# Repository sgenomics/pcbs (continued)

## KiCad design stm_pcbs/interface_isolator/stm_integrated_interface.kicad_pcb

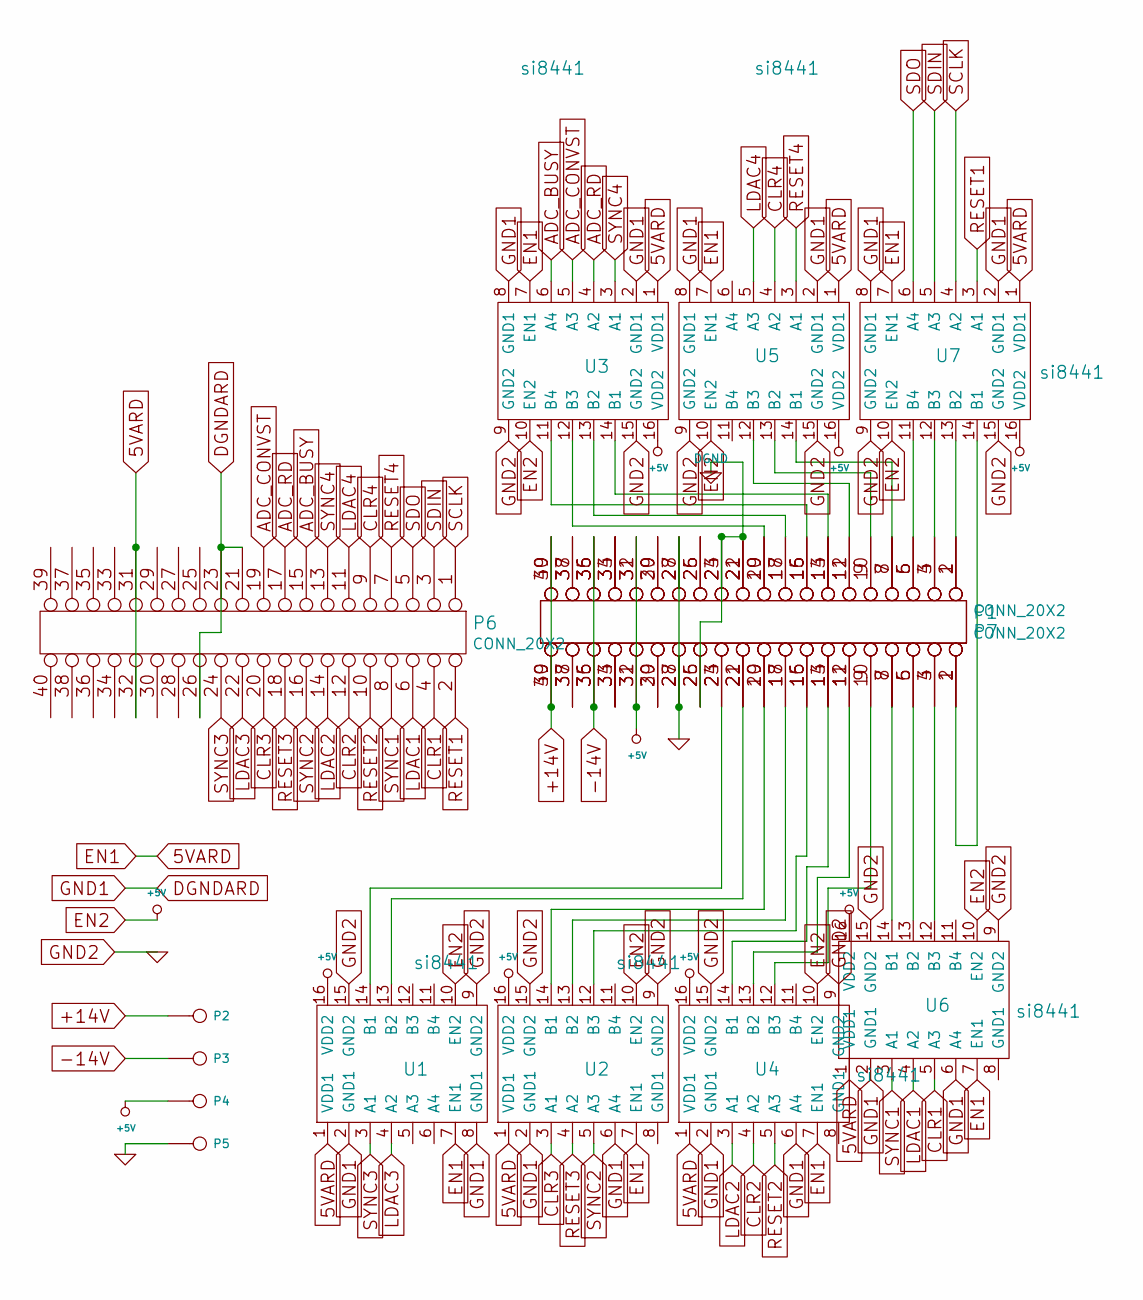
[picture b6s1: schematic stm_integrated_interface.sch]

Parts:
P1, P6, P7: CONN_20X2; IDC-Header_2x20_Pitch2.54mm_Straight
P2, P3, P4, P5: CONN_1; 4mm_banana
U1, U2, U3, U4, U5, U6, U7: si8441; SOIC-16W_7.5x10.3mm_Pitch1.27mm

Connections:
5VARD: P6.31, P6.32, U1.1 (VDD1), U1.7 (EN1), U2.1 (VDD1), U2.7 (EN1), U3.1 (VDD1), U3.7 (EN1), U4.1 (VDD1), U4.7 (EN1), U5.1 (VDD1), U5.7 (EN1), U6.1 (VDD1), U6.7 (EN1), U7.1 (VDD1), U7.7 (EN1)
+14V: P1.39, P1.40, P2.1, P7.39, P7.40
-14V: P1.35, P1.36, P3.1, P7.35, P7.36
ADC_BUSY: P6.15, U3.6 (A4)
ADC_CONVST: P6.19, U3.5 (A3)
ADC_RD: P6.17, U3.4 (A2)
CLR1: P6.4, U6.5 (A3)
CLR2: P6.12, U4.4 (A2)
CLR3: P6.20, U2.3 (A1)
CLR4: P6.9, U5.4 (A2)
DGND: P1.21, P1.23, P1.26, P7.22, P7.24, P7.25
DGNDARD: P6.21, P6.23, P6.26, U1.2 (GND1), U1.8 (GND1), U2.2 (GND1), U2.6 (A4), U3.2 (GND1), U3.8 (GND1), U4.2 (GND1), U4.6 (A4), U5.2 (GND1), U5.8 (GND1), U6.2 (GND1), U6.6 (A4), U7.2 (GND1), U7.8 (GND1)
EN2: P1.31, P1.32, P4.1, P7.31, P7.32, U1.10 (EN2), U1.16 (VDD2), U2.10 (EN2), U2.16 (VDD2), U3.10 (EN2), U3.16 (VDD2), U4.10 (EN2), U4.16 (VDD2), U5.10 (EN2), U5.16 (VDD2), U6.10 (EN2), U6.16 (VDD2), U7.10 (EN2), U7.16 (VDD2)
GND2: P1.27, P1.28, P5.1, P7.27, P7.28, U1.9 (GND2), U1.15 (GND2), U2.9 (GND2), U2.15 (GND2), U3.9 (GND2), U3.15 (GND2), U4.9 (GND2), U4.15 (GND2), U5.9 (GND2), U5.15 (GND2), U6.9 (GND2), U6.15 (GND2), U7.9 (GND2), U7.15 (GND2)
LDAC1: P6.6, U6.4 (A2)
LDAC2: P6.14, U4.3 (A1)
LDAC3: P6.22, U1.4 (A2)
LDAC4: P6.11, U5.5 (A3)
unnamed: P1.1, P7.2, U7.13 (B2)
unnamed: P1.2, P7.1, U7.14 (B1)
unnamed: P1.3, P7.4, U7.12 (B3)
unnamed: P1.4, P7.3, U6.12 (B3)
unnamed: P1.5, P7.6, U7.11 (B4)
unnamed: P1.6, P7.5, U6.13 (B2)
unnamed: P1.7, P7.8, U5.14 (B1)
unnamed: P1.8, P7.7, U6.14 (B1)
unnamed: P1.9, P7.10, U5.13 (B2)
unnamed: P1.10, P7.9, U4.12 (B3)
unnamed: P1.11, P7.12, U5.12 (B3)
unnamed: P1.12, P7.11, U4.13 (B2)
unnamed: P1.13, P7.14, U3.14 (B1)
unnamed: P1.14, P7.13, U4.14 (B1)
unnamed: P1.15, P7.16, U3.11 (B4)
unnamed: P1.16, P7.15, U2.12 (B3)
unnamed: P1.17, P7.18, U3.13 (B2)
unnamed: P1.18, P7.17, U2.13 (B2)
unnamed: P1.19, P7.20, U3.12 (B3)
unnamed: P1.20, P7.19, U2.14 (B1)
unnamed: P1.22, P7.21, U1.13 (B2)
unnamed: P1.24, P7.23, U1.14 (B1)
unnamed: P1.25, P7.26
unnamed: P1.29, P7.30
unnamed: P1.30, P7.29
unnamed: P1.33, P7.34
unnamed: P1.34, P7.33
unnamed: P1.37, P7.38
unnamed: P1.38, P7.37
RESET1: P6.2, U7.3 (A1)
RESET2: P6.10, U4.5 (A3)
RESET3: P6.18, U2.4 (A2)
RESET4: P6.7, U5.3 (A1)
SCLK: P6.1, U7.4 (A2)
SDIN: P6.3, U7.5 (A3)
SDO: P6.5, U7.6 (A4)
SYNC1: P6.8, U6.3 (A1)
SYNC2: P6.16, U2.5 (A3)
SYNC3: P6.24, U1.3 (A1)
SYNC4: P6.13, U3.3 (A1)

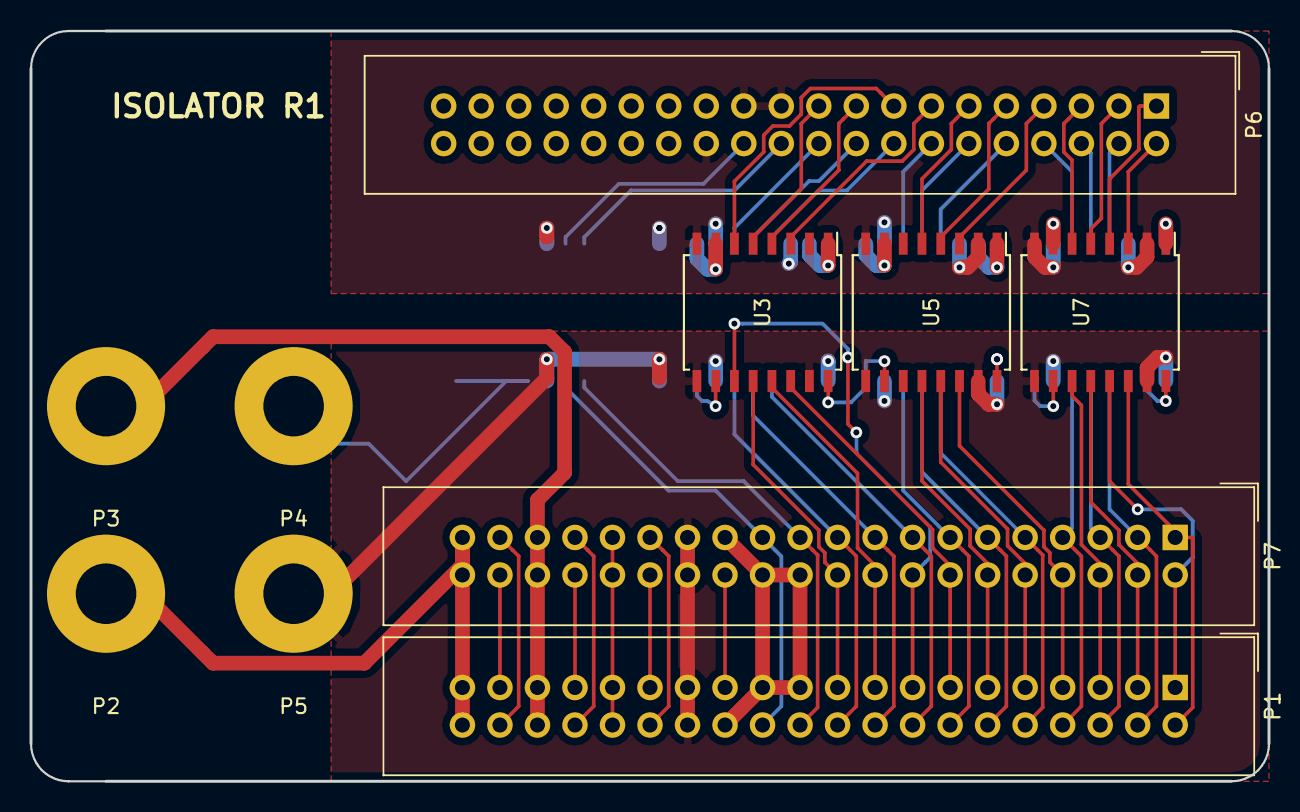
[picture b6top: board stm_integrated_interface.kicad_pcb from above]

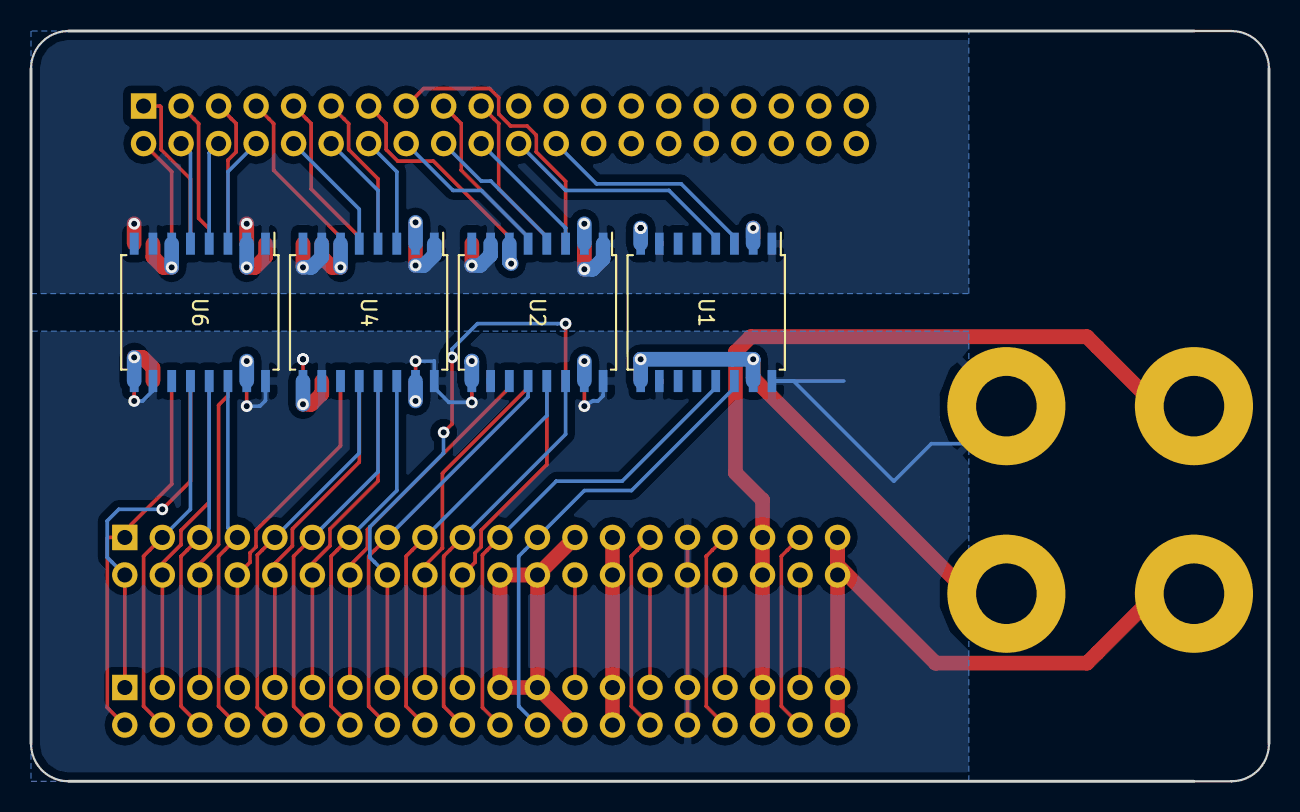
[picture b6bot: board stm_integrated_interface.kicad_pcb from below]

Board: 2 copper layers, 83.8 x 50.8 mm, 14 parts (4 on the bottom side), 58 nets.

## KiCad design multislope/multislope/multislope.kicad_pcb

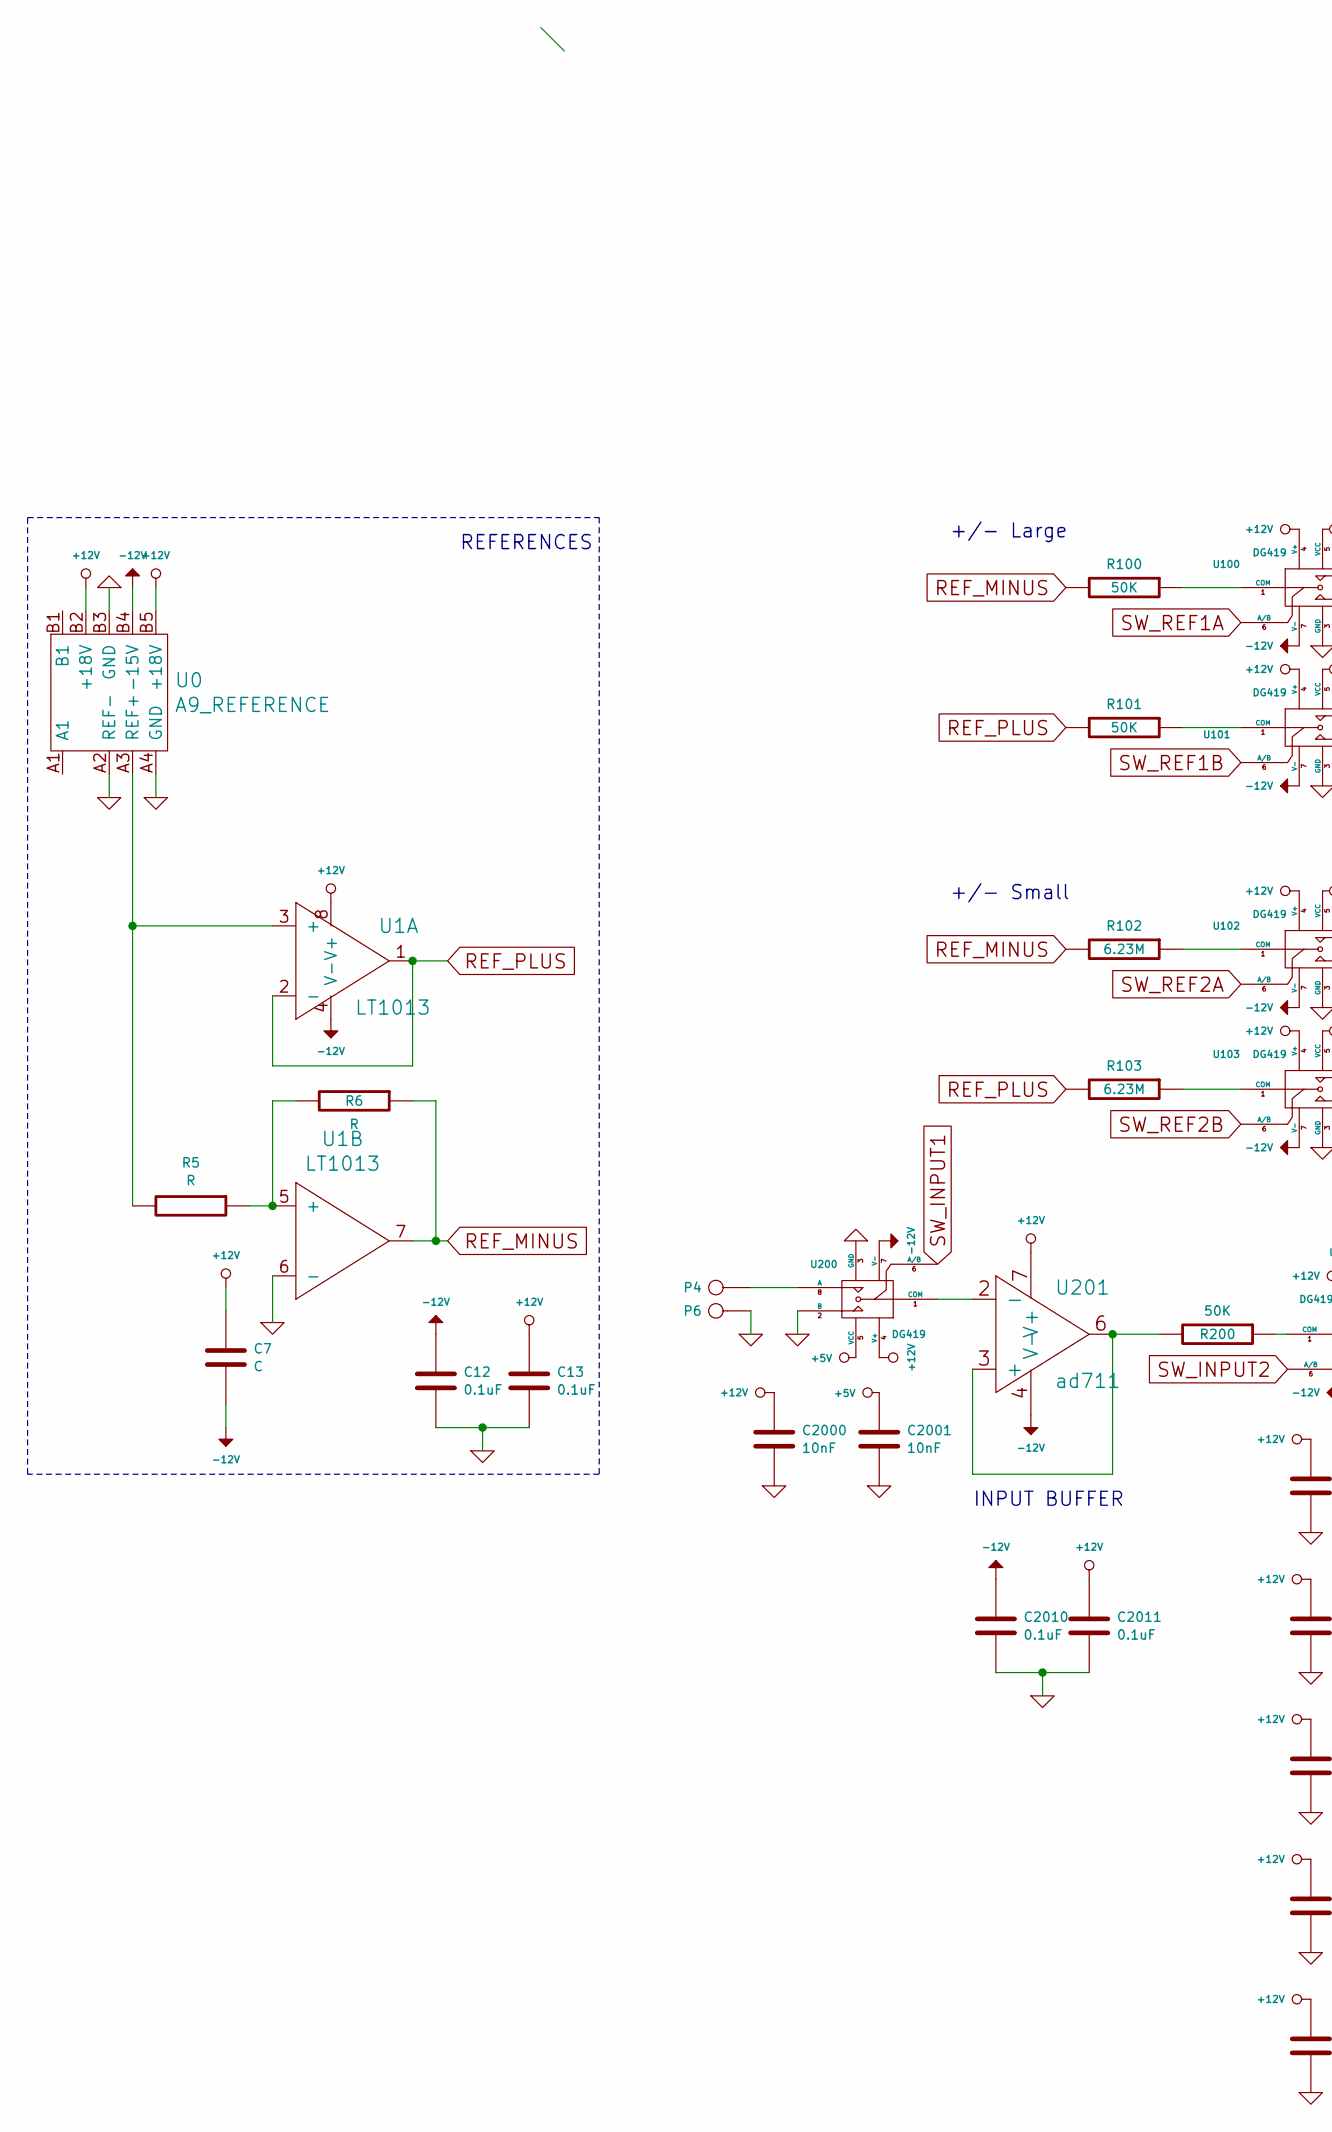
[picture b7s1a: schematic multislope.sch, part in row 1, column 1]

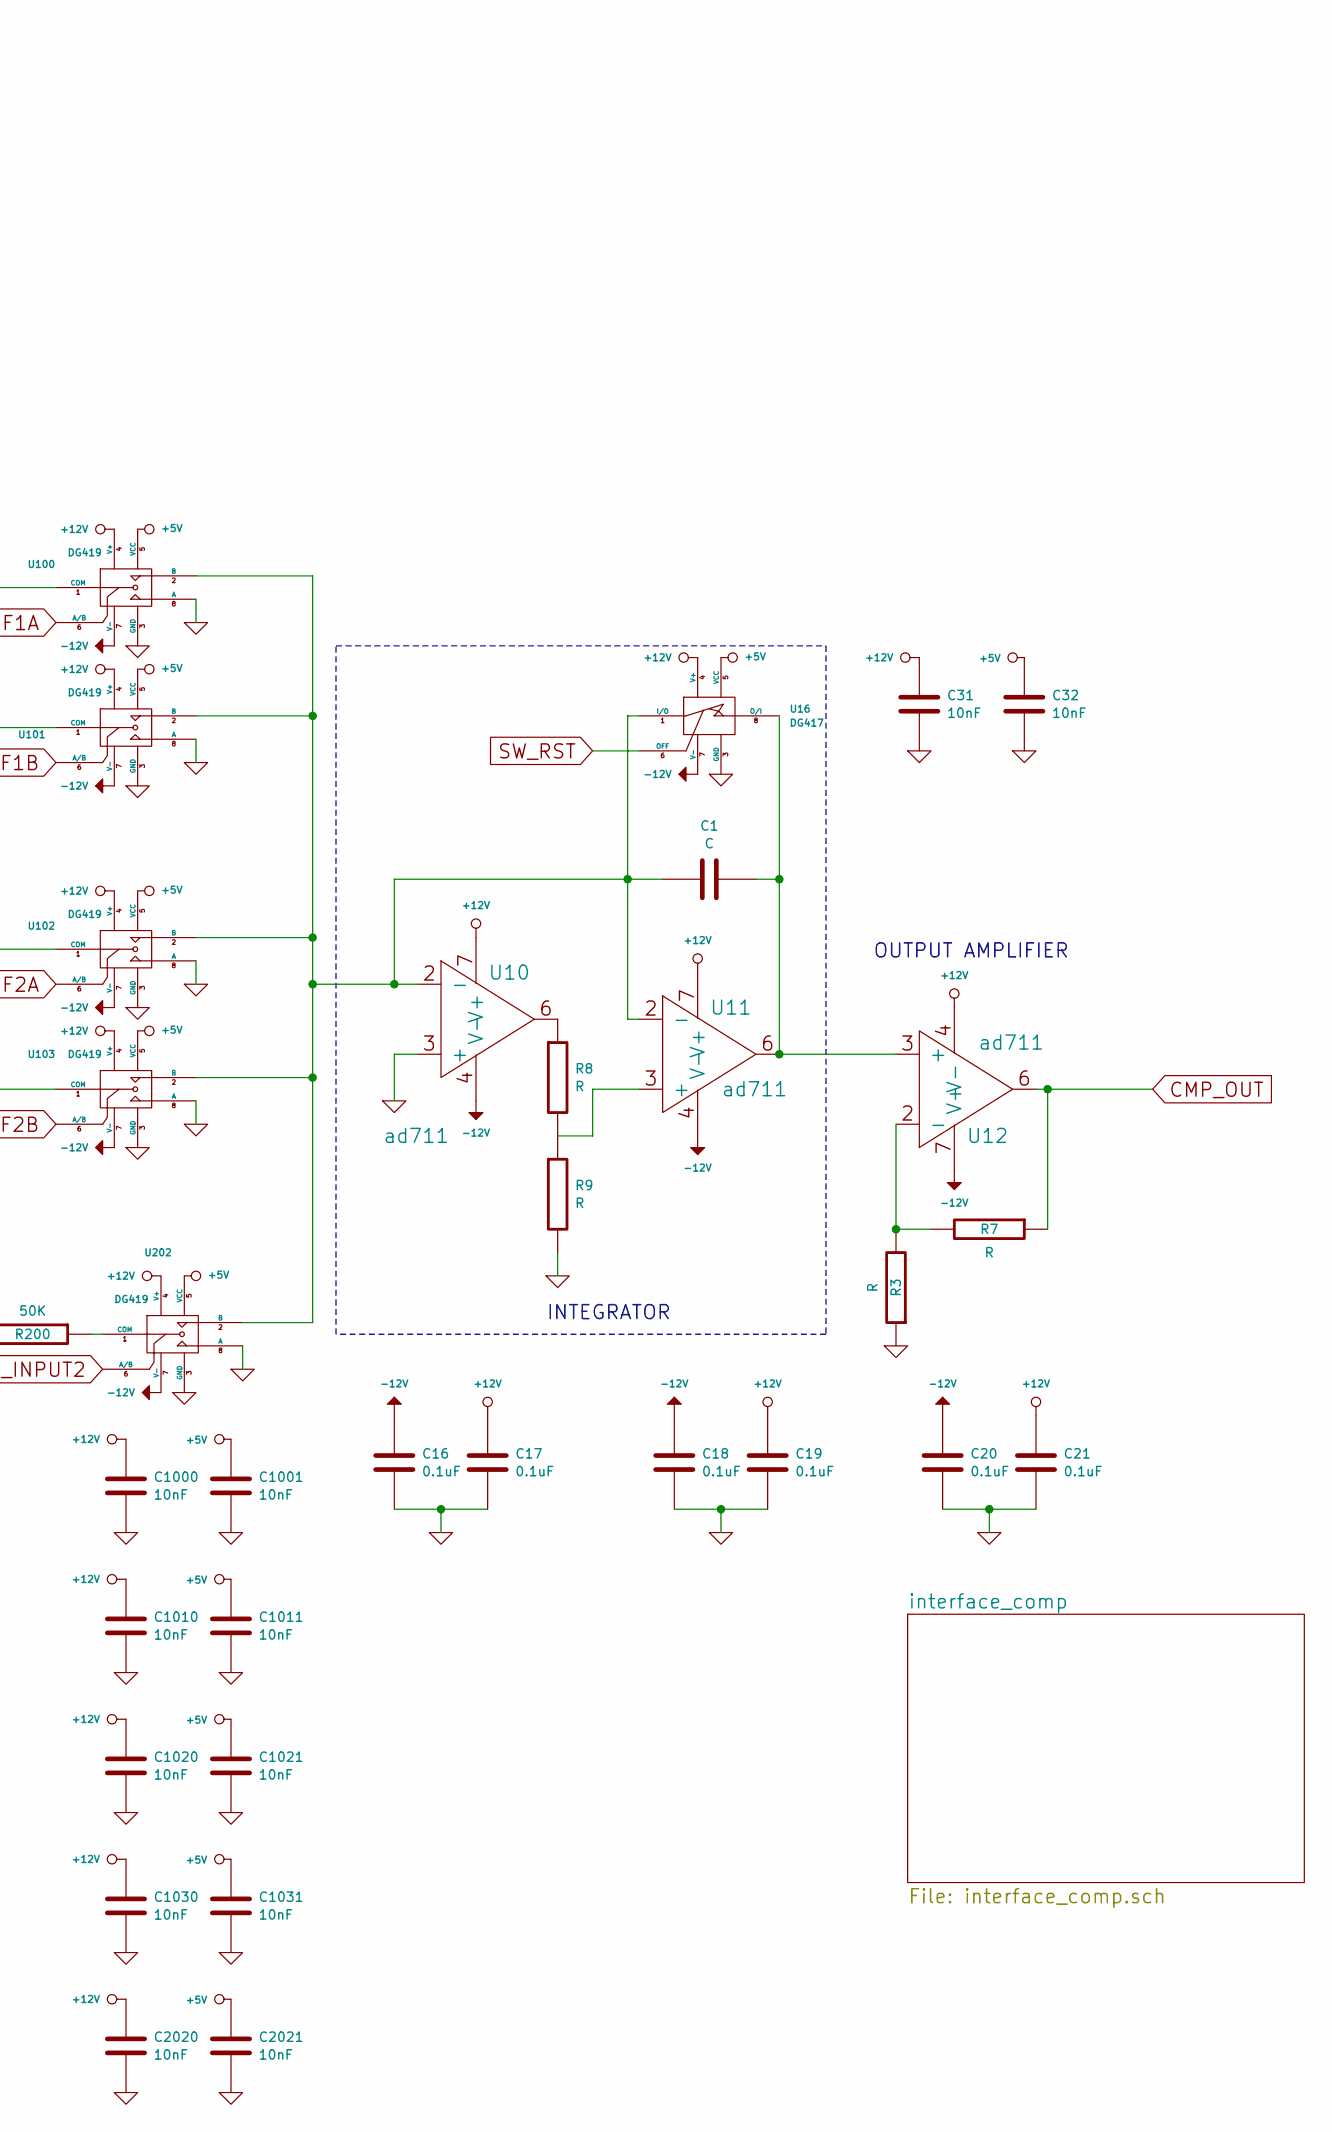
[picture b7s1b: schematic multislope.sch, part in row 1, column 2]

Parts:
C1, C7: C; C_1206_HandSoldering
C12, C13, C16, C17, C18, C19, C20, C21, C2010, C2011: 0.1uF; C_1206_HandSoldering
C31, C32, C1000, C1001, C1010, C1011, C1020, C1021, C1030, C1031, C2000, C2001, C2020, C2021: 10nF; C_1206_HandSoldering
P4, P6: CONN_1; 4mm_banana
R3, R5, R6, R7, R8, R9: R; R_Axial_DIN0207_L6.3mm_D2.5mm_P10.16mm_Horizontal
R100, R101, R200: 50K; R_Axial_DIN0207_L6.3mm_D2.5mm_P10.16mm_Horizontal
R102, R103: 6.23M; R_Axial_DIN0207_L6.3mm_D2.5mm_P10.16mm_Horizontal
U0: A9_REFERENCE; A9REFERENCE
U1: LT1013; DIP-8_W7.62mm
U10, U11, U12, U201: ad711; DIP-8_W7.62mm
U16: DG417; MSOP-8_3x3mm_Pitch0.65mm
U100, U101, U102, U103, U200, U202: DG419; MSOP-8_3x3mm_Pitch0.65mm

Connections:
+5V: C32.1, C1001.1, C1011.1, C1021.1, C1031.1, C2001.1, C2021.1, U16.5 (VCC), U100.5 (VCC), U101.5 (VCC), U102.5 (VCC), U103.5 (VCC), U200.5 (VCC), U202.5 (VCC); also elsewhere on the board
+12V: C7.2, C13.1, C17.1, C19.1, C21.1, C31.1, C1000.1, C1010.1, C1020.1, C1030.1, C2000.1, C2011.1, C2020.1, U0.B2 (+18V), U0.B5 (+18V), U1.8 (V+), U10.7 (V+), U11.7 (V+), U12.4 (V-), U16.4 (V+), U100.4 (V+), U101.4 (V+), U102.4 (V+), U103.4 (V+), U200.4 (V+), U201.7 (V+), U202.4 (V+); also elsewhere on the board
-12V: C7.1, C12.1, C16.1, C18.1, C20.1, C2010.1, U0.B4 (-15V), U1.4 (V-), U10.4 (V-), U11.4 (V-), U12.7 (V+), U16.7 (V-), U100.7 (V-), U101.7 (V-), U102.7 (V-), U103.7 (V-), U200.7 (V-), U201.4 (V-), U202.7 (V-); also elsewhere on the board
CMP_OUT: R7.1, U12.6; also elsewhere on the board
GND: C12.2, C13.2, C16.2, C17.2, C18.2, C19.2, C20.2, C21.2, C31.2, C32.2, C1000.2, C1001.2, C1010.2, C1011.2, C1020.2, C1021.2, C1030.2, C1031.2, C2000.2, C2001.2, C2010.2, C2011.2, C2020.2, C2021.2, P6.1, R3.1, R9.2, U0.A2 (REF-), U0.A4 (GND), U0.B3 (GND), U1.6 (-), U10.3 (+), U16.3 (GND), U100.3 (GND), U100.8 (A), U101.3 (GND), U101.8 (A), U102.3 (GND), U102.8 (A), U103.3 (GND), U103.8 (A), U200.2 (B), U200.3 (GND), U202.3 (GND), U202.8 (A); also elsewhere on the board
unnamed: C1.1, U11.6, U12.3 (+), U16.8 (O/I)
unnamed: C1.2, U10.2 (-), U11.2 (-), U16.1 (I/O), U100.2 (B), U101.2 (B), U102.2 (B), U103.2 (B), U202.2 (B)
unnamed: P4.1, U200.8 (A)
unnamed: R3.2, R7.2, U12.2 (-)
unnamed: R5.1, R6.2, U1.5 (+)
unnamed: R5.2, U0.A3 (REF+), U1.3 (+)
unnamed: R8.1, U10.6
unnamed: R8.2, R9.1, U11.3 (+)
unnamed: R100.1, U100.1 (COM)
unnamed: R101.1, U101.1 (COM)
unnamed: R102.1, U102.1 (COM)
unnamed: R103.1, U103.1 (COM)
unnamed: R200.1, U202.1 (COM)
unnamed: R200.2, U201.3 (+), U201.6
unnamed: U200.1 (COM), U201.2 (-)
REF_MINUS: R6.1, R100.2, R102.2, U1.7
REF_PLUS: R101.2, R103.2, U1.1, U1.2 (-)
SW_INPUT1: U200.6 (A/B); also elsewhere on the board
SW_INPUT2: U202.6 (A/B); also elsewhere on the board
SW_REF1A: U100.6 (A/B); also elsewhere on the board
SW_REF1B: U101.6 (A/B); also elsewhere on the board
SW_REF2A: U102.6 (A/B); also elsewhere on the board
SW_REF2B: U103.6 (A/B); also elsewhere on the board
SW_RST: U16.6 (OFF); also elsewhere on the board

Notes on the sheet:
REFERENCES
OUTPUT AMPLIFIER
INTEGRATOR
INPUT BUFFER
+/- Large
+/- Small

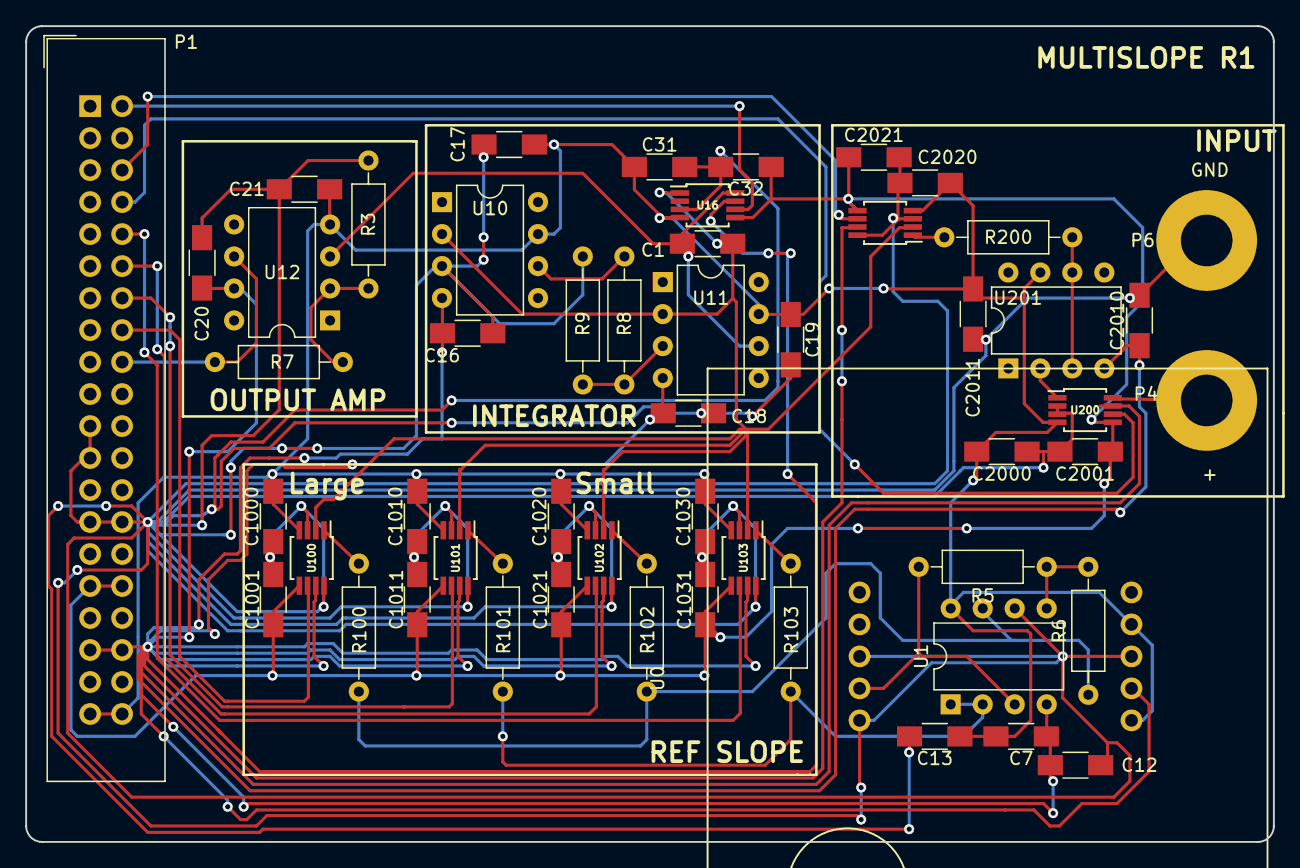
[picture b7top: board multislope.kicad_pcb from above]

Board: 2 copper layers, 99.1 x 64.8 mm, 53 parts (0 on the bottom side), 29 nets.

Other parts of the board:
P1: CONN_20X2; IDC-Header_2x20_Pitch2.54mm_Straight

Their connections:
+5V: P1.31, P1.32; also elsewhere on the board
+12V: P1.39, P1.40; also elsewhere on the board
-12V: P1.35, P1.36; also elsewhere on the board
CMP_OUT: P1.18; also elsewhere on the board
GND: P1.21, P1.23, P1.27, P1.28; also elsewhere on the board
SW_INPUT1: P1.8; also elsewhere on the board
SW_INPUT2: P1.6; also elsewhere on the board
SW_REF1A: P1.16; also elsewhere on the board
SW_REF1B: P1.14; also elsewhere on the board
SW_REF2A: P1.12; also elsewhere on the board
SW_REF2B: P1.10; also elsewhere on the board
SW_RST: P1.2; also elsewhere on the board

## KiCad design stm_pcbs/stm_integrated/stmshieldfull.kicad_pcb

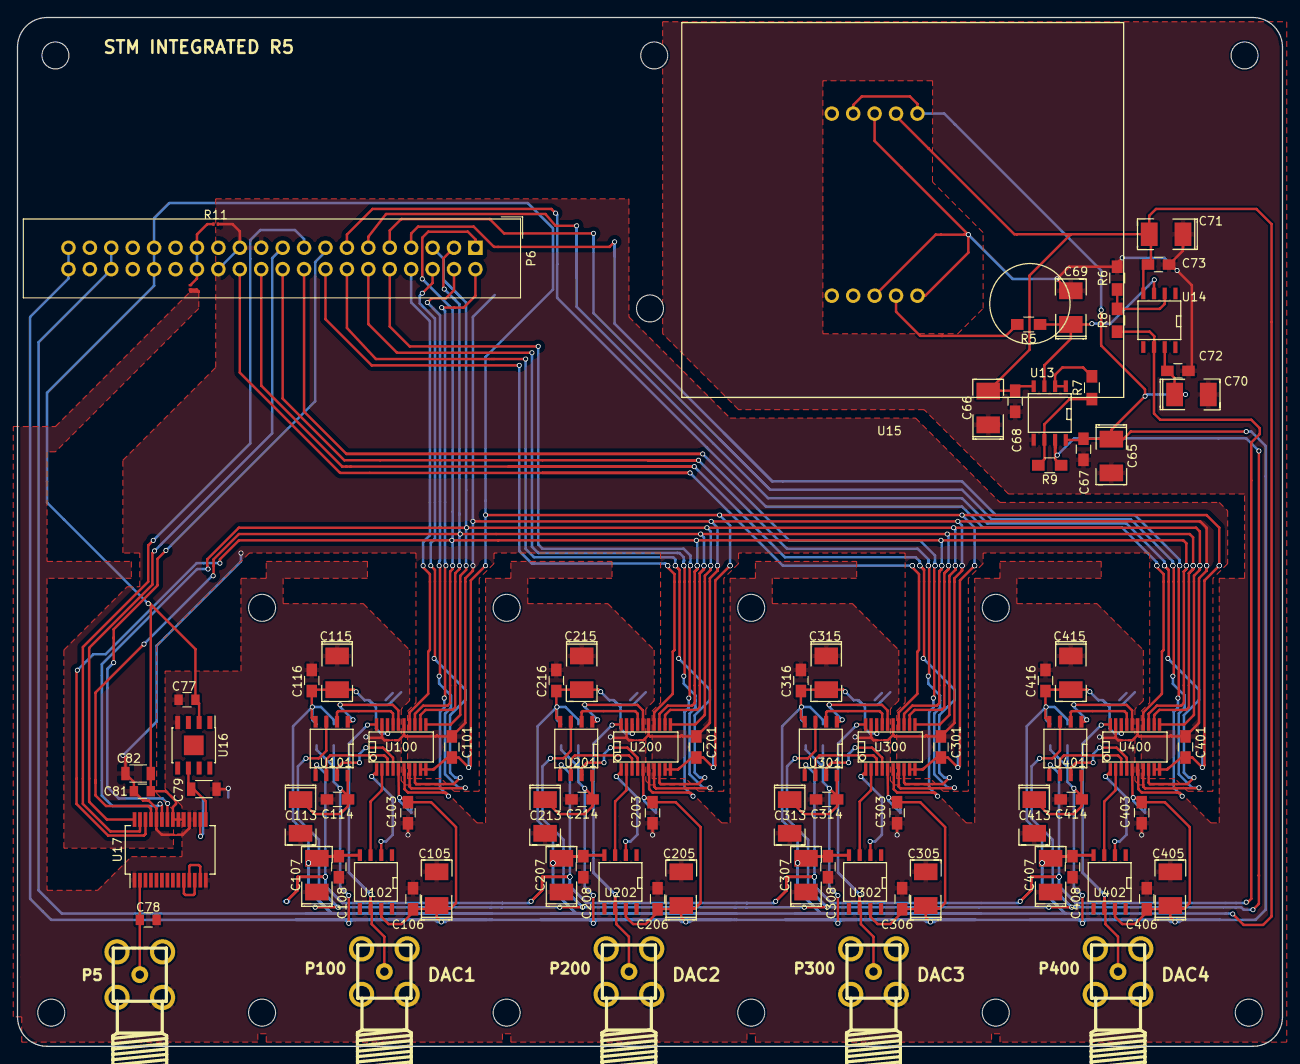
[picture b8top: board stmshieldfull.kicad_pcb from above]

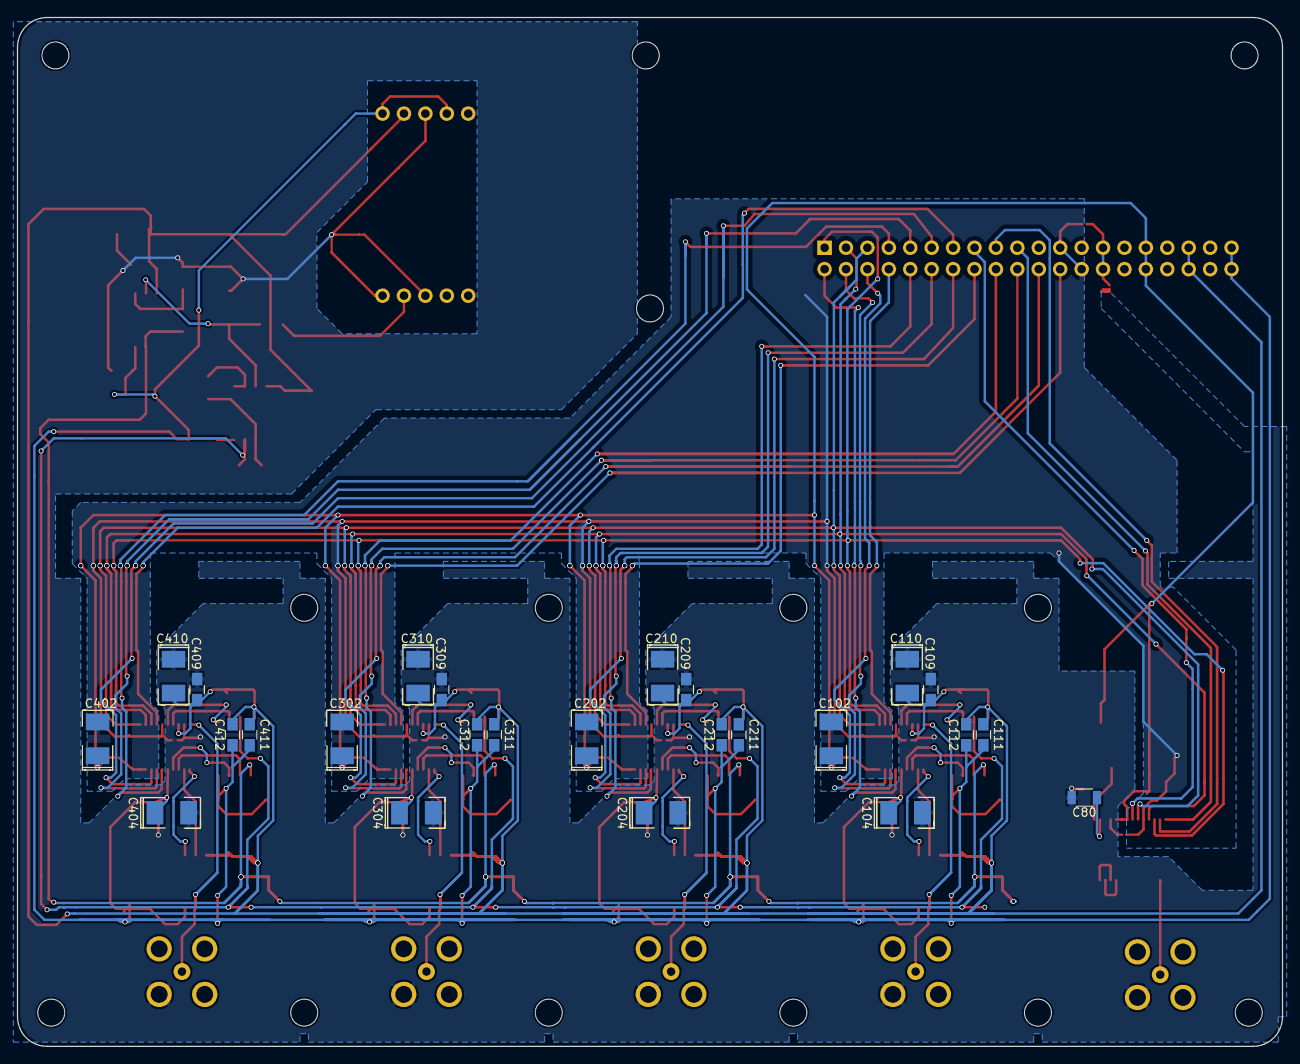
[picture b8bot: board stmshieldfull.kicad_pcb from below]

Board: 2 copper layers, 150.0 x 122.0 mm, 114 parts (25 on the bottom side), 68 nets.

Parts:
C65, C66, C69, C70, C71, C102, C104, C105, C107, C110, C113, C115, C202, C204, C205, C207, C210, C213, C215, C302, C304, C305, C307, C310, C313, C315, C402, C404, C405, C407, C410, C413, C415: 10uF; SMD-1210_Pol
C67, C68, C72, C73, C101, C103, C106, C108, C109, C111, C112, C114, C116, C201, C203, C206, C208, C209, C211, C212, C214, C216, C301, C303, C306, C308, C309, C311, C312, C314, C316, C401, C403, C406, C408, C409, C411, C412, C414, C416: 0.1uF; C_0805_HandSoldering
C77, C81: 0.1uF; C_0805
C78: 1000pF; C_0805
C79: 4.7uF; C_1206
C80, C82: 10uF; C_1206
P5, P100, P200, P300, P400: BNC; SMA
P6: CONN_20X2; IDC-Header_2x20_Pitch2.54mm_Straight
R5: 1.5k; R_0805_HandSoldering
R6: 2k5; R_0805_HandSoldering
R7: 10K; R_0805_HandSoldering
R8: 1K; R_0805_HandSoldering
R9: 14K; R_0805_HandSoldering
R10, R100, R200, R300, R400: 0; 0Ohm
R11, R12: 0; R_0201_NoSilk
U13, U101, U201, U301, U401: AD8676; SOIC-8
U14, U102, U202, U302, U402: AD8675; SOIC-8
U15: A9_REFERENCE; A9REFERENCE
U16: LT1019ACS8; SOIC-8-1EP_3.9x4.9mm_Pitch1.27mm
U17: LTC1859; SSOP-28_5.3x10.2mm_Pitch0.65mm
U100, U200, U300, U400: AD5791; SSOP-20

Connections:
7VREF: R5.2, U15.A3
+5V: C77.1, C81.1, C82.1, C101.2, C102.1, C201.2, C202.1, C301.2, C302.1, C401.2, C402.1, P6.31, P6.32, U16.2, U17.19, U17.20, U17.21, U100.9, U100.10, U200.9, U200.10, U300.9, U300.10, U400.9, U400.10
+10VREF: R8.1, U14.6, U101.5, U201.5, U301.5, U401.5
+14V: C65.1, C67.1, C70.1, C72.1, C103.2, C104.1, C105.1, C106.1, C111.1, C112.1, C113.1, C114.1, C203.2, C204.1, C205.1, C206.1, C211.1, C212.1, C213.1, C214.1, C303.2, C304.1, C305.1, C306.1, C311.1, C312.1, C313.1, C314.1, C403.2, C404.1, C405.1, C406.1, C411.1, C412.1, C413.1, C414.1, P6.39, P6.40, U13.8, U14.7, U15.B2, U15.B5, U100.5, U101.8, U102.7, U200.5, U201.8, U202.7, U300.5, U301.8, U302.7, U400.5, U401.8, U402.7
-10VREF: R9.1, U13.7, U101.3, U201.3, U301.3, U401.3
-14V: C66.2, C68.1, C71.2, C73.1, C107.2, C108.1, C109.2, C110.2, C111.2, C112.2, C115.2, C116.1, C207.2, C208.1, C209.2, C210.2, C211.2, C212.2, C215.2, C216.1, C307.2, C308.1, C309.2, C310.2, C311.2, C312.2, C315.2, C316.1, C407.2, C408.1, C409.2, C410.2, C411.2, C412.2, C415.2, C416.1, P6.35, P6.36, U13.4, U14.4, U15.B4, U100.18, U101.4, U102.4, U200.18, U201.4, U202.4, U300.18, U301.4, U302.4, U400.18, U401.4, U402.4
ADC_BUSY: P6.15, U17.22
ADC_CONVST: P6.19, U17.28
ADC_RD: P6.17, U17.27
AGND: C65.2, C66.1, C67.2, C68.2, C69.2, C70.2, C71.1, C72.2, C73.2, C77.2, C78.2, C79.2, C80.2, C103.1, C104.2, C105.2, C106.2, C107.1, C108.2, C109.1, C110.1, C113.2, C114.2, C115.1, C116.2, C203.1, C204.2, C205.2, C206.2, C207.1, C208.2, C209.1, C210.1, C213.2, C214.2, C215.1, C216.2, C303.1, C304.2, C305.2, C306.2, C307.1, C308.2, C309.1, C310.1, C313.2, C314.2, C315.1, C316.2, C403.1, C404.2, C405.2, C406.2, C407.1, C408.2, C409.1, C410.1, C413.2, C414.2, C415.1, C416.2, P5.2, P100.2, P200.2, P300.2, P400.2, R6.2, R10.2, R12.2, R100.2, R200.2, R300.2, R400.2, U13.5, U15.A2, U15.A4, U15.B3, U16.4, U17.1, U17.14, U17.17, U17.18, U100.19, U200.19, U300.19, U400.19
CLR1: P6.4, U100.7
CLR2: P6.12, U200.7
CLR3: P6.20, U300.7
CLR4: P6.9, U400.7
DGND: C81.2, C82.2, C101.1, C102.2, C201.1, C202.2, C301.1, C302.2, C401.1, C402.2, P6.21, P6.23, P6.26, R10.1, R11.2, R100.1, R200.1, R300.1, R400.1, U17.24, U100.15, U200.15, U300.15, U400.15
GND: P6.27, P6.28, R11.1, R12.1
LDAC1: P6.6, U100.8
LDAC2: P6.14, U200.8
LDAC3: P6.22, U300.8
LDAC4: P6.11, U400.8
unnamed: C69.1, R5.1, U13.3, U14.3
unnamed: C78.1, P5.1, U17.2
unnamed: C79.1, U16.6, U17.15
unnamed: C80.1, U17.16
unnamed: P100.1, U100.20, U102.6
unnamed: P200.1, U200.20, U202.6
unnamed: P300.1, U300.20, U302.6
unnamed: P400.1, U400.20, U402.6
unnamed: R6.1, R8.2, U14.2
unnamed: R7.1, R9.2, U13.6
unnamed: R7.2, U13.1, U13.2
unnamed: U17.10, U17.12
unnamed: U17.11, U17.13
unnamed: U100.1, U102.2
unnamed: U100.2, U102.3
unnamed: U100.3, U101.6
unnamed: U100.4, U101.7
unnamed: U100.16, U101.1
unnamed: U100.17, U101.2
unnamed: U200.1, U202.2
unnamed: U200.2, U202.3
unnamed: U200.3, U201.6
unnamed: U200.4, U201.7
unnamed: U200.16, U201.1
unnamed: U200.17, U201.2
unnamed: U300.1, U302.2
unnamed: U300.2, U302.3
unnamed: U300.3, U301.6
unnamed: U300.4, U301.7
unnamed: U300.16, U301.1
unnamed: U300.17, U301.2
unnamed: U400.1, U402.2
unnamed: U400.2, U402.3
unnamed: U400.3, U401.6
unnamed: U400.4, U401.7
unnamed: U400.16, U401.1
unnamed: U400.17, U401.2
RESET1: P6.2, U100.6
RESET2: P6.10, U200.6
RESET3: P6.18, U300.6
RESET4: P6.7, U400.6
SCLK: P6.1, U17.26, U100.13, U200.13, U300.13, U400.13
SDIN: P6.3, U17.25, U100.12, U200.12, U300.12, U400.12
SDO: P6.5, U17.23, U100.11, U200.11, U300.11, U400.11
SYNC1: P6.8, U100.14
SYNC2: P6.16, U200.14
SYNC3: P6.24, U300.14
SYNC4: P6.13, U400.14

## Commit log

2016-05-05 initial commit of all pcbs
2016-05-06 missing link to antenna and ground
2016-05-06 added gerber pack
2016-05-06 made track thicker
2016-05-08 ch340 lib
2016-05-08 r6 version (with ch340)
2016-05-08 updated microsd footprint and relaid board
2016-09-24 current version
2016-09-28 misssing files
2016-09-29 Dual esp board
2016-10-01 added esp32 usb
2016-10-07 updated tsop48er to r2 (changed zif socket)
2017-01-20 Adding missing boards/reorged
2017-04-04 misc
2017-12-02 added stm integrated
2017-12-03 working on Kicad of 3rd Dec
2017-12-03 fixing more borkage
2017-12-03 tidying up boards, adding all DAC signals.
2017-12-08 Using LTZ1000 (A9 board)
2017-12-08 added A9 reference
2017-12-26 fixed issue with DAC (opamp wiring was wrong)
2017-12-29 update stm integrated design based on bring up...
2017-12-29 added multislope and a9ref
2017-12-29 current
2018-01-02 Trying FETs, two opamps in integrator
2018-01-03 current multislope
2018-01-05 ad g# new file: stm_pcbs/interface_isolator/arduino_shields.dcm
2018-12-26 DDC112 board, multislope and various other updates it seems
2020-02-10 Linear CCD project
2020-08-24 Mostly Chua's stuff
2020-11-05 Added new power connector
2021-03-16 added break CBD stuff, updated chua's
